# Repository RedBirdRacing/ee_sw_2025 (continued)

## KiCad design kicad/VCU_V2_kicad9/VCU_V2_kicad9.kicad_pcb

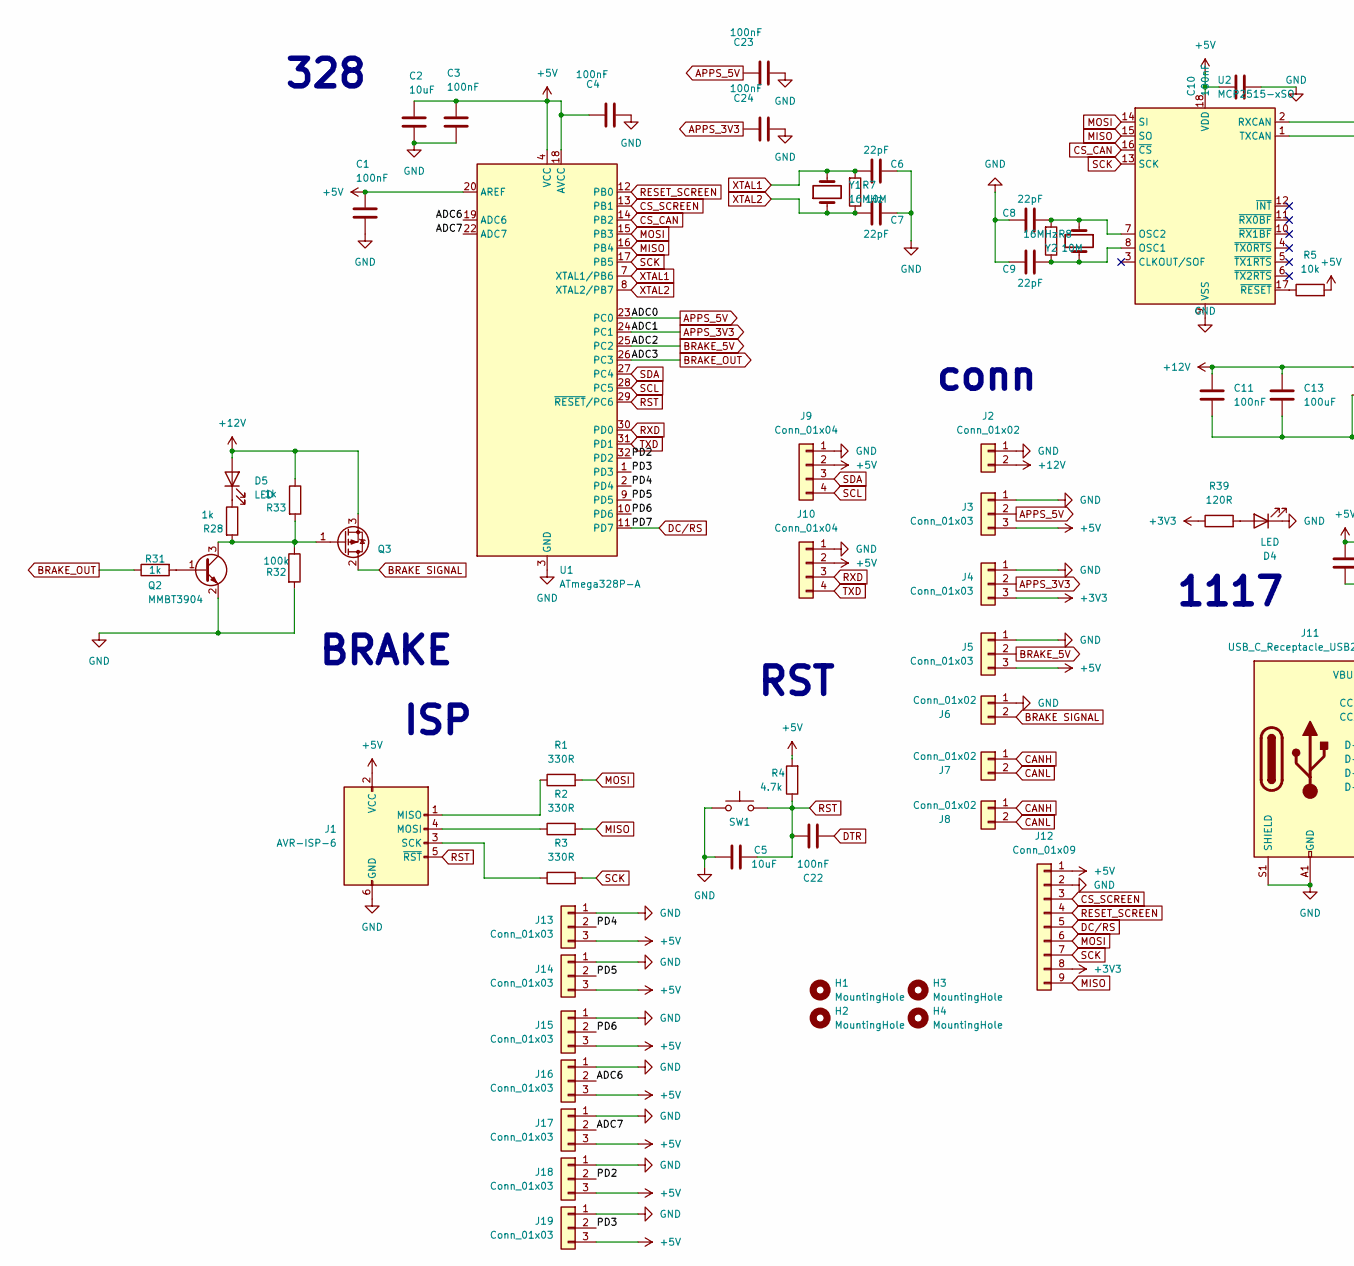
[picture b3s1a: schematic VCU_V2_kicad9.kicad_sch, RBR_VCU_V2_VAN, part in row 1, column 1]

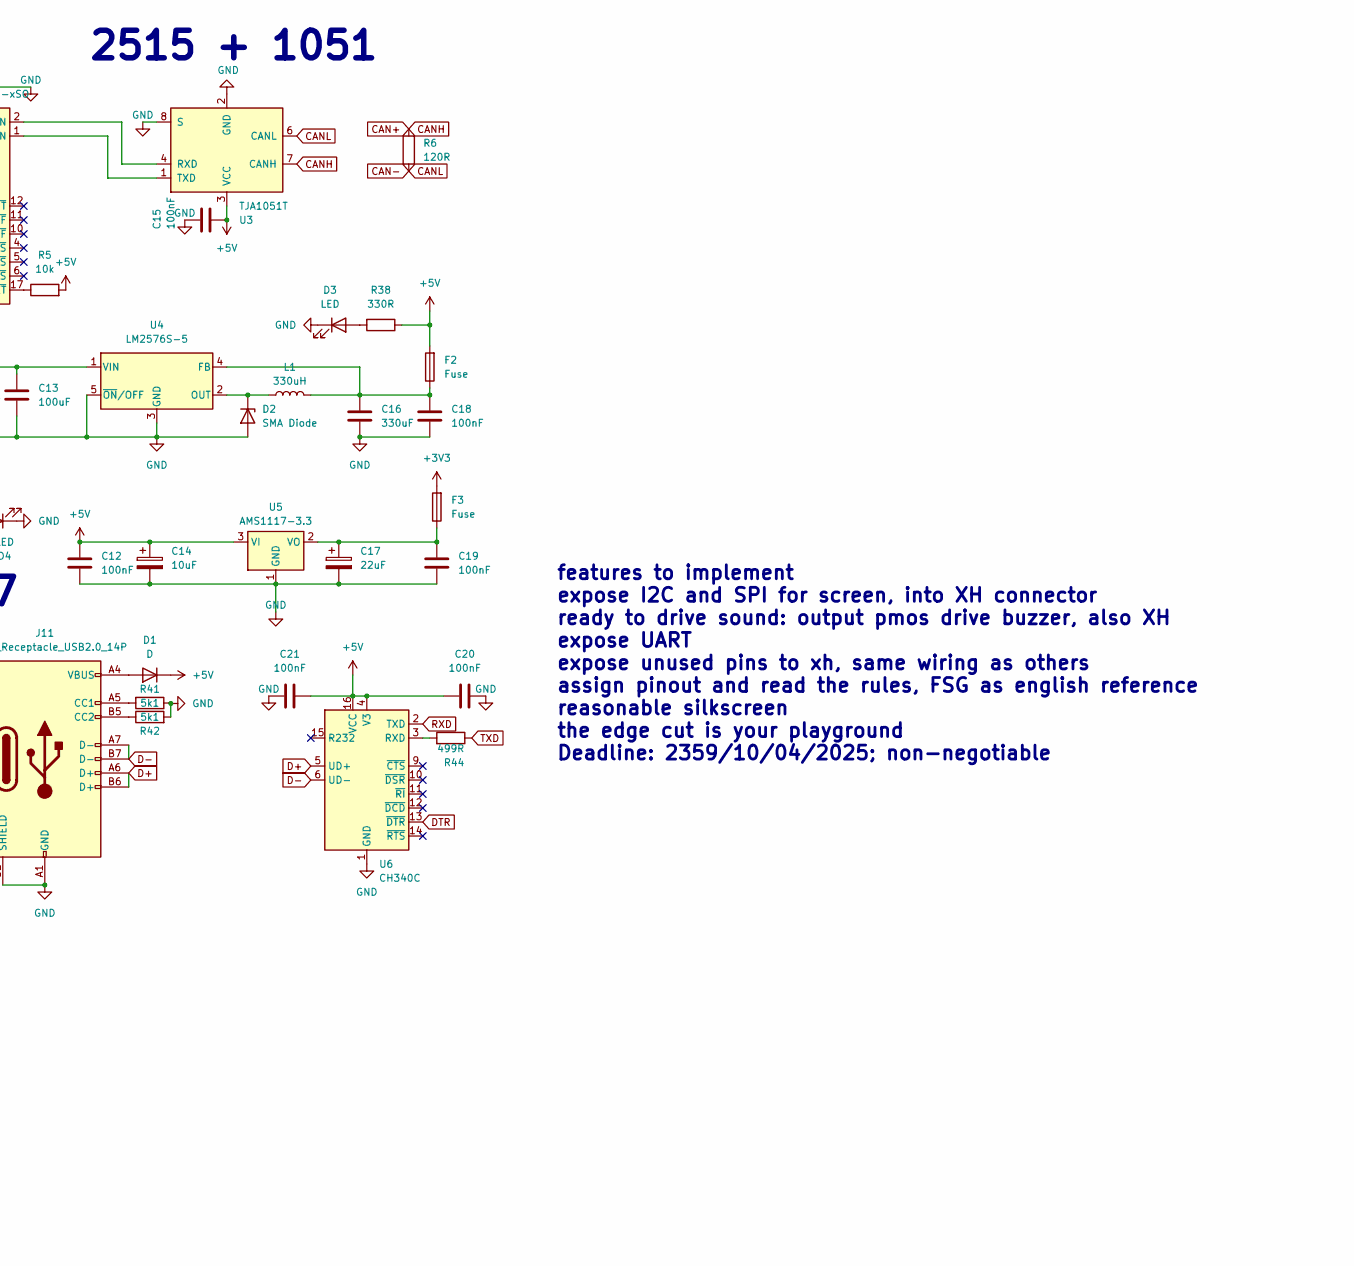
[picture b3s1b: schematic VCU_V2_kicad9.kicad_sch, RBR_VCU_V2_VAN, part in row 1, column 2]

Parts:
C1, C3, C4, C10, C11, C12, C15, C18, C19, C20, C21, C22, C23, C24: 100nF; C_0805_2012Metric_Pad1.18x1.45mm_HandSolder_L
C2, C5, C14: 10uF; C_0805_2012Metric_Pad1.18x1.45mm_HandSolder_L
C6, C7, C8, C9: 22pF; C_0805_2012Metric_Pad1.18x1.45mm_HandSolder_L
C13: 100uF; CP_Radial_D6.3mm_P2.50mm
C16: 330uF; CP_Radial_D6.3mm_P2.50mm
C17: 22uF; C_0805_2012Metric_Pad1.18x1.45mm_HandSolder_L
D1: D; D_SMA_Handsoldering
D2: SMA Diode; D_SMA_Handsoldering
D3, D4, D5: LED; LED_0805_2012Metric_Pad1.45x1.40mm_HandSolder
F2, F3: Fuse; Fuse_1210_3225Metric_Pad1.42x2.65mm_HandSolder
H1, H2, H3, H4: MountingHole; MountingHole_3.2mm_M3
J1: AVR-ISP-6; PinHeader_2x03_P2.54mm_Vertical
J2: Conn_01x02; JST_VH_B2P-VH-B_1x02_P3.96mm_Vertical
J3, J4, J5, J13, J14, J15, J16, J17, J18, J19: Conn_01x03; JST_XH_B3B-XH-A_1x03_P2.50mm_Vertical
J6, J7, J8: Conn_01x02; JST_XH_B2B-XH-A_1x02_P2.50mm_Vertical
J9, J10: Conn_01x04; JST_XH_B4B-XH-A_1x04_P2.50mm_Vertical
J11: USB_C_Receptacle_USB2.0_14P; USB_C_Receptacle_G-Switch_GT-USB-7010ASV_Handsolder
J12: Conn_01x09; JST_XH_B9B-XH-A_1x09_P2.50mm_Vertical
L1: 330uH; L_10.4x10.4_H4.8
Q2: MMBT3904; SOT-23
Q3: TO-252 PMOS; TO-252-2
R1, R2, R3, R38: 330R; R_0805_2012Metric_Pad1.20x1.40mm_HandSolder_L
R4: 4.7k; R_0805_2012Metric_Pad1.20x1.40mm_HandSolder_L
R5: 10k; R_0805_2012Metric_Pad1.20x1.40mm_HandSolder_L
R6, R39: 120R; R_0805_2012Metric_Pad1.20x1.40mm_HandSolder_L
R7, R8: 10M; R_0805_2012Metric_Pad1.20x1.40mm_HandSolder_L
R28, R31, R33: 1k; R_0805_2012Metric_Pad1.20x1.40mm_HandSolder_L
R32: 100k; R_0805_2012Metric_Pad1.20x1.40mm_HandSolder_L
R41, R42: 5k1; R_0805_2012Metric_Pad1.20x1.40mm_HandSolder_L
R44: 499R; R_0805_2012Metric_Pad1.20x1.40mm_HandSolder_L
SW1: SW_Push; SW_PUSH_6mm_H5mm
U1: ATmega328P-A; TQFP-32_7x7mm_P0.8mm_L
U2: MCP2515-xSO; SOIC-18W_7.5x11.6mm_P1.27mm_L
U3: TJA1051T; SOIC-8_3.9x4.9mm_P1.27mm_RMC_Handsolder
U4: LM2576S-5; TO-263-5_TabPin3_Handsolder
U5: AMS1117-3.3; SOT-223-3_TabPin2_Handsolder
U6: CH340C; SOIC-16_3.9x9.9mm_P1.27mm_Handsolder
Y1, Y2: 16MHz; Crystal_HC49-U_Vertical_W_SMD

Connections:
+3V3: F3.2, J4.3, J12.8, R39.1
+5V: C1.2, C2.2, C3.2, C4.2, C10.2, C12.1, C14.1, C15.1, C20.1, C21.2, D1.1 (K), F2.2, J1.2 (VCC), J3.3, J5.3, J9.2, J10.2, J12.1, J13.3, J14.3, J15.3, J16.3, J17.3, J18.3, J19.3, R4.2, R5.2, R38.1, U1.4 (VCC), U1.6 (VCC), U1.18 (AVCC), U1.20 (AREF), U2.18 (VDD), U3.3 (VCC), U5.3 (VI), U6.4 (V3), U6.16 (VCC)
+12V: C11.2, C13.1, D5.2 (A), J2.2, Q3.3 (S), R33.1, U4.1 (VIN)
/ADC6: J16.2, U1.19 (ADC6)
/ADC7: J17.2, U1.22 (ADC7)
/PD2: J18.2, U1.32 (PD2)
/PD3: J19.2, U1.1 (PD3)
/PD4: J13.2, U1.2 (PD4)
/PD5: J14.2, U1.9 (PD5)
/PD6: J15.2, U1.10 (PD6)
APPS_3V3: C24.2, J4.2, U1.24 (PC1)
APPS_5V: C23.2, J3.2, U1.23 (PC0)
BRAKE SIGNAL: J6.2, Q3.2 (D)
BRAKE_5V: J5.2, U1.25 (PC2)
BRAKE_OUT: R31.1, U1.26 (PC3)
CAN+: J7.1, J8.1, R6.2, U3.7 (CANH)
CAN-: J7.2, J8.2, R6.1, U3.6 (CANL)
CS_CAN: U1.14 (PB2), U2.16 (~CS)
CS_SCREEN: J12.3, U1.13 (PB1)
D+: J11.A6 (D+), J11.B6 (D+), U6.5 (UD+)
D-: J11.A7 (D-), J11.B7 (D-), U6.6 (UD-)
DC/RS: J12.5, U1.11 (PD7)
DTR: C22.1, U6.13 (~DTR)
GND: C1.1, C2.1, C3.1, C4.1, C5.1, C6.1, C7.1, C8.1, C9.1, C10.1, C11.1, C12.2, C13.2, C14.2, C15.2, C16.2, C17.2, C18.1, C19.2, C20.2, C21.1, C23.1, C24.1, D2.2 (A), D3.1 (K), D4.1 (K), J1.6 (GND), J2.1, J3.1, J4.1, J5.1, J6.1, J9.1, J10.1, J11.A1 (GND), J11.A12 (GND), J11.B1 (GND), J11.B12 (GND), J11.S1 (SHIELD), J12.2, J13.1, J14.1, J15.1, J16.1, J17.1, J18.1, J19.1, Q2.2 (E), R32.2, R41.1, R42.2, SW1.1, U1.3 (GND), U1.5 (GND), U1.21 (GND), U2.9 (VSS), U3.2 (GND), U3.8 (S), U4.3 (GND), U4.5 (~ON/OFF), U5.1 (GND), U6.1 (GND)
MISO: J12.9, R2.2, U1.16 (PB4), U2.15 (SO)
MOSI: J12.6, R1.2, U1.15 (PB3), U2.14 (SI)
unnamed: D1.2 (A), J11.A4 (VBUS), J11.A9 (VBUS), J11.B4 (VBUS), J11.B9 (VBUS)
unnamed: D2.1 (K), L1.1, U4.2 (OUT)
unnamed: D3.2 (A), R38.2
unnamed: D4.2 (A), R39.2
unnamed: D5.1 (K), R28.1
unnamed: J1.1 (MISO), R1.1
unnamed: J1.4 (MOSI), R2.1
unnamed: J1.3 (SCK), R3.1
unnamed: J11.A5 (CC1), R41.2
unnamed: J11.B5 (CC2), R42.1
unnamed: Q2.1 (B), R31.2
unnamed: Q2.3 (C), Q3.1 (G), R28.2, R32.1, R33.2
unnamed: C9.2, R8.1, U2.8 (OSC1), Y2.2
unnamed: C8.2, R8.2, U2.7 (OSC2), Y2.1
unnamed: U2.2 (RXCAN), U3.4 (RXD)
unnamed: U2.1 (TXCAN), U3.1 (TXD)
unnamed: R5.1, U2.17 (~RESET)
unnamed: C16.1, C18.2, F2.1, L1.2, U4.4 (FB)
unnamed: C17.1, C19.1, F3.1, U5.2 (VO)
unnamed: R44.2, U6.3 (RXD)
RESET_SCREEN: J12.4, U1.12 (PB0)
RST: C5.2, C22.2, J1.5 (~RST), R4.1, SW1.2, U1.29 (~RESET/PC6)
RXD: J10.3, U1.30 (PD0), U6.2 (TXD)
SCK: J12.7, R3.2, U1.17 (PB5), U2.13 (SCK)
SCL: J9.4, U1.28 (PC5)
SDA: J9.3, U1.27 (PC4)
TXD: J10.4, R44.1, U1.31 (PD1)
XTAL1: C6.2, R7.2, U1.7 (XTAL1/PB6), Y1.2
XTAL2: C7.2, R7.1, U1.8 (XTAL2/PB7), Y1.1

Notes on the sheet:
RST
conn
ISP
1117
2515 + 1051
features to implement expose I2C and SPI for screen, into XH connector ready to drive sound: output pmos drive buzzer, also XH expose UART expose unused pins to xh, same wiring as others assign pinout and read the rules, FSG as english reference reasonable silkscreen the edge cut is your playground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
BRAKE
328

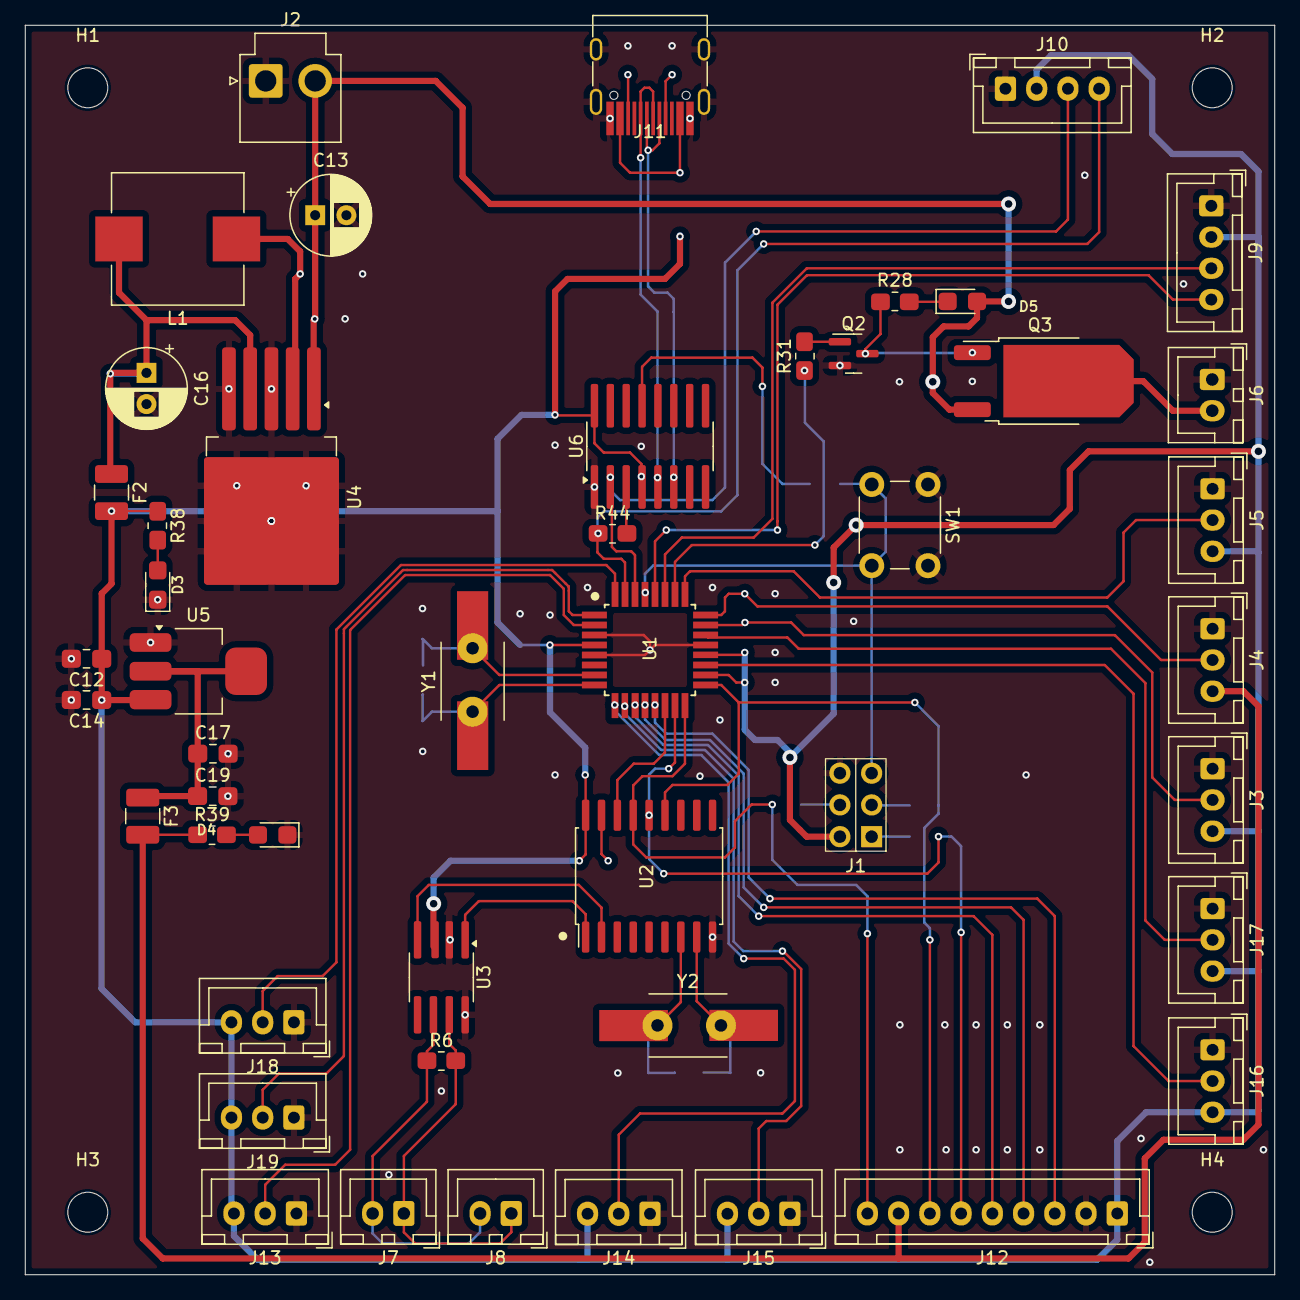
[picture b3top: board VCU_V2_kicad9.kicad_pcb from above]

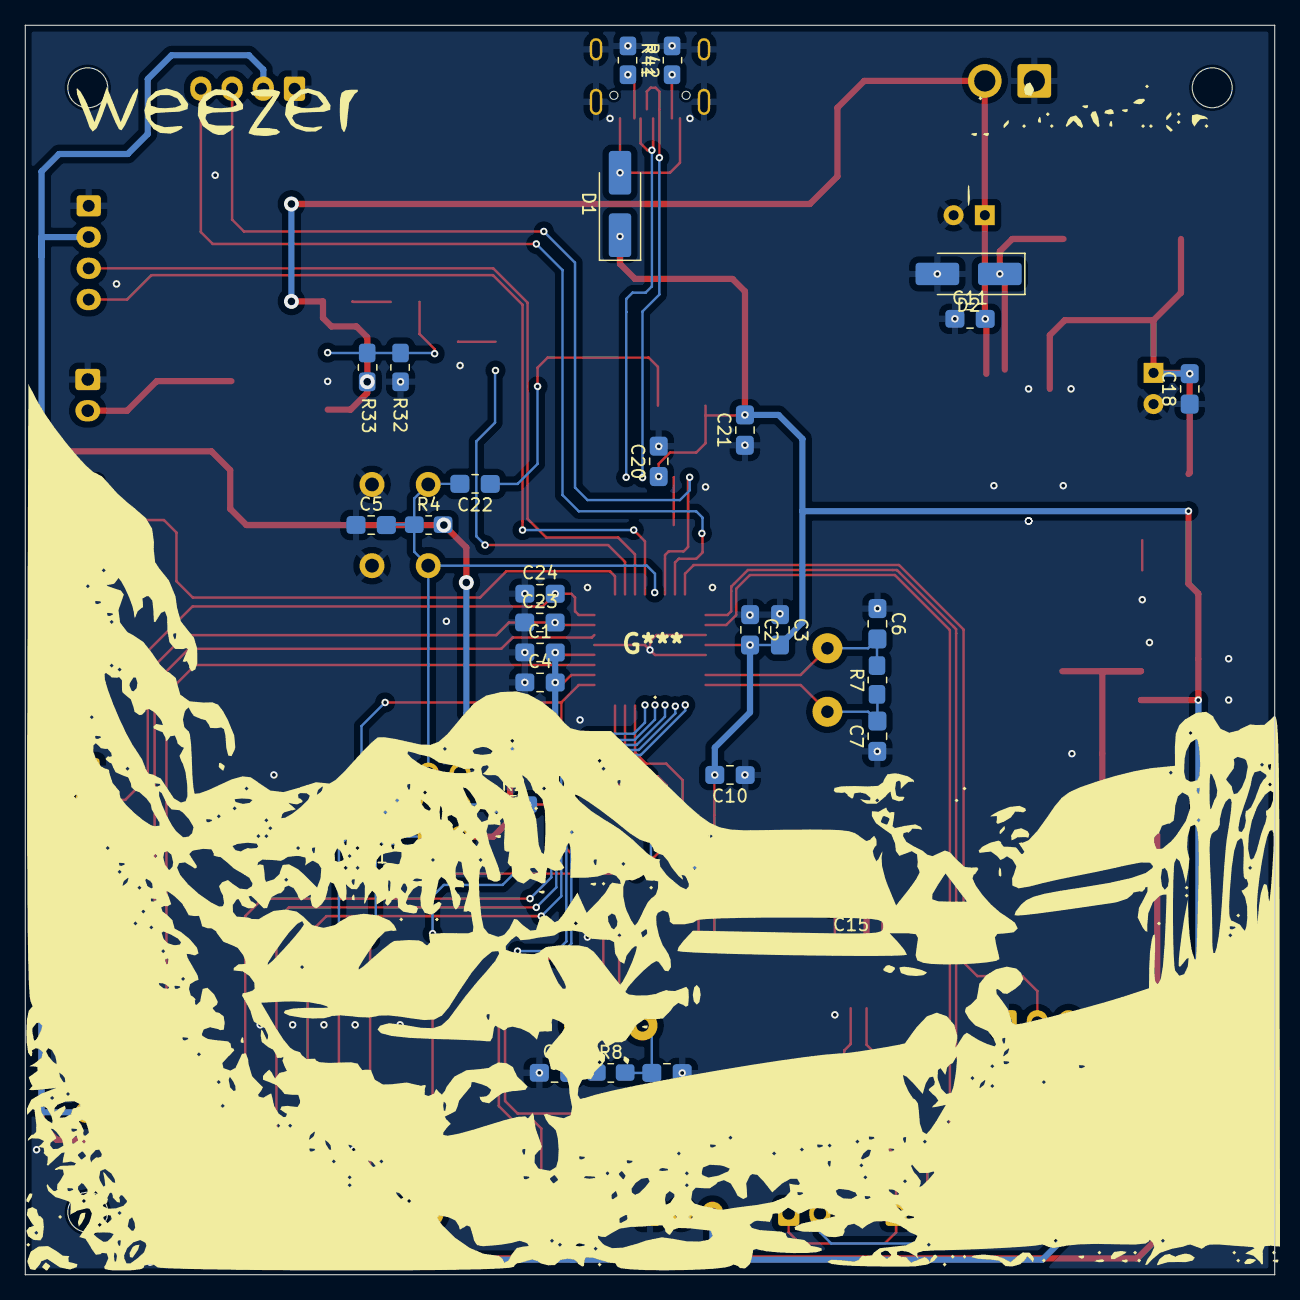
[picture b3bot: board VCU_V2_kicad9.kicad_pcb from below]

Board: 2 copper layers, 100.0 x 100.0 mm, 83 parts (31 on the bottom side), 55 nets.

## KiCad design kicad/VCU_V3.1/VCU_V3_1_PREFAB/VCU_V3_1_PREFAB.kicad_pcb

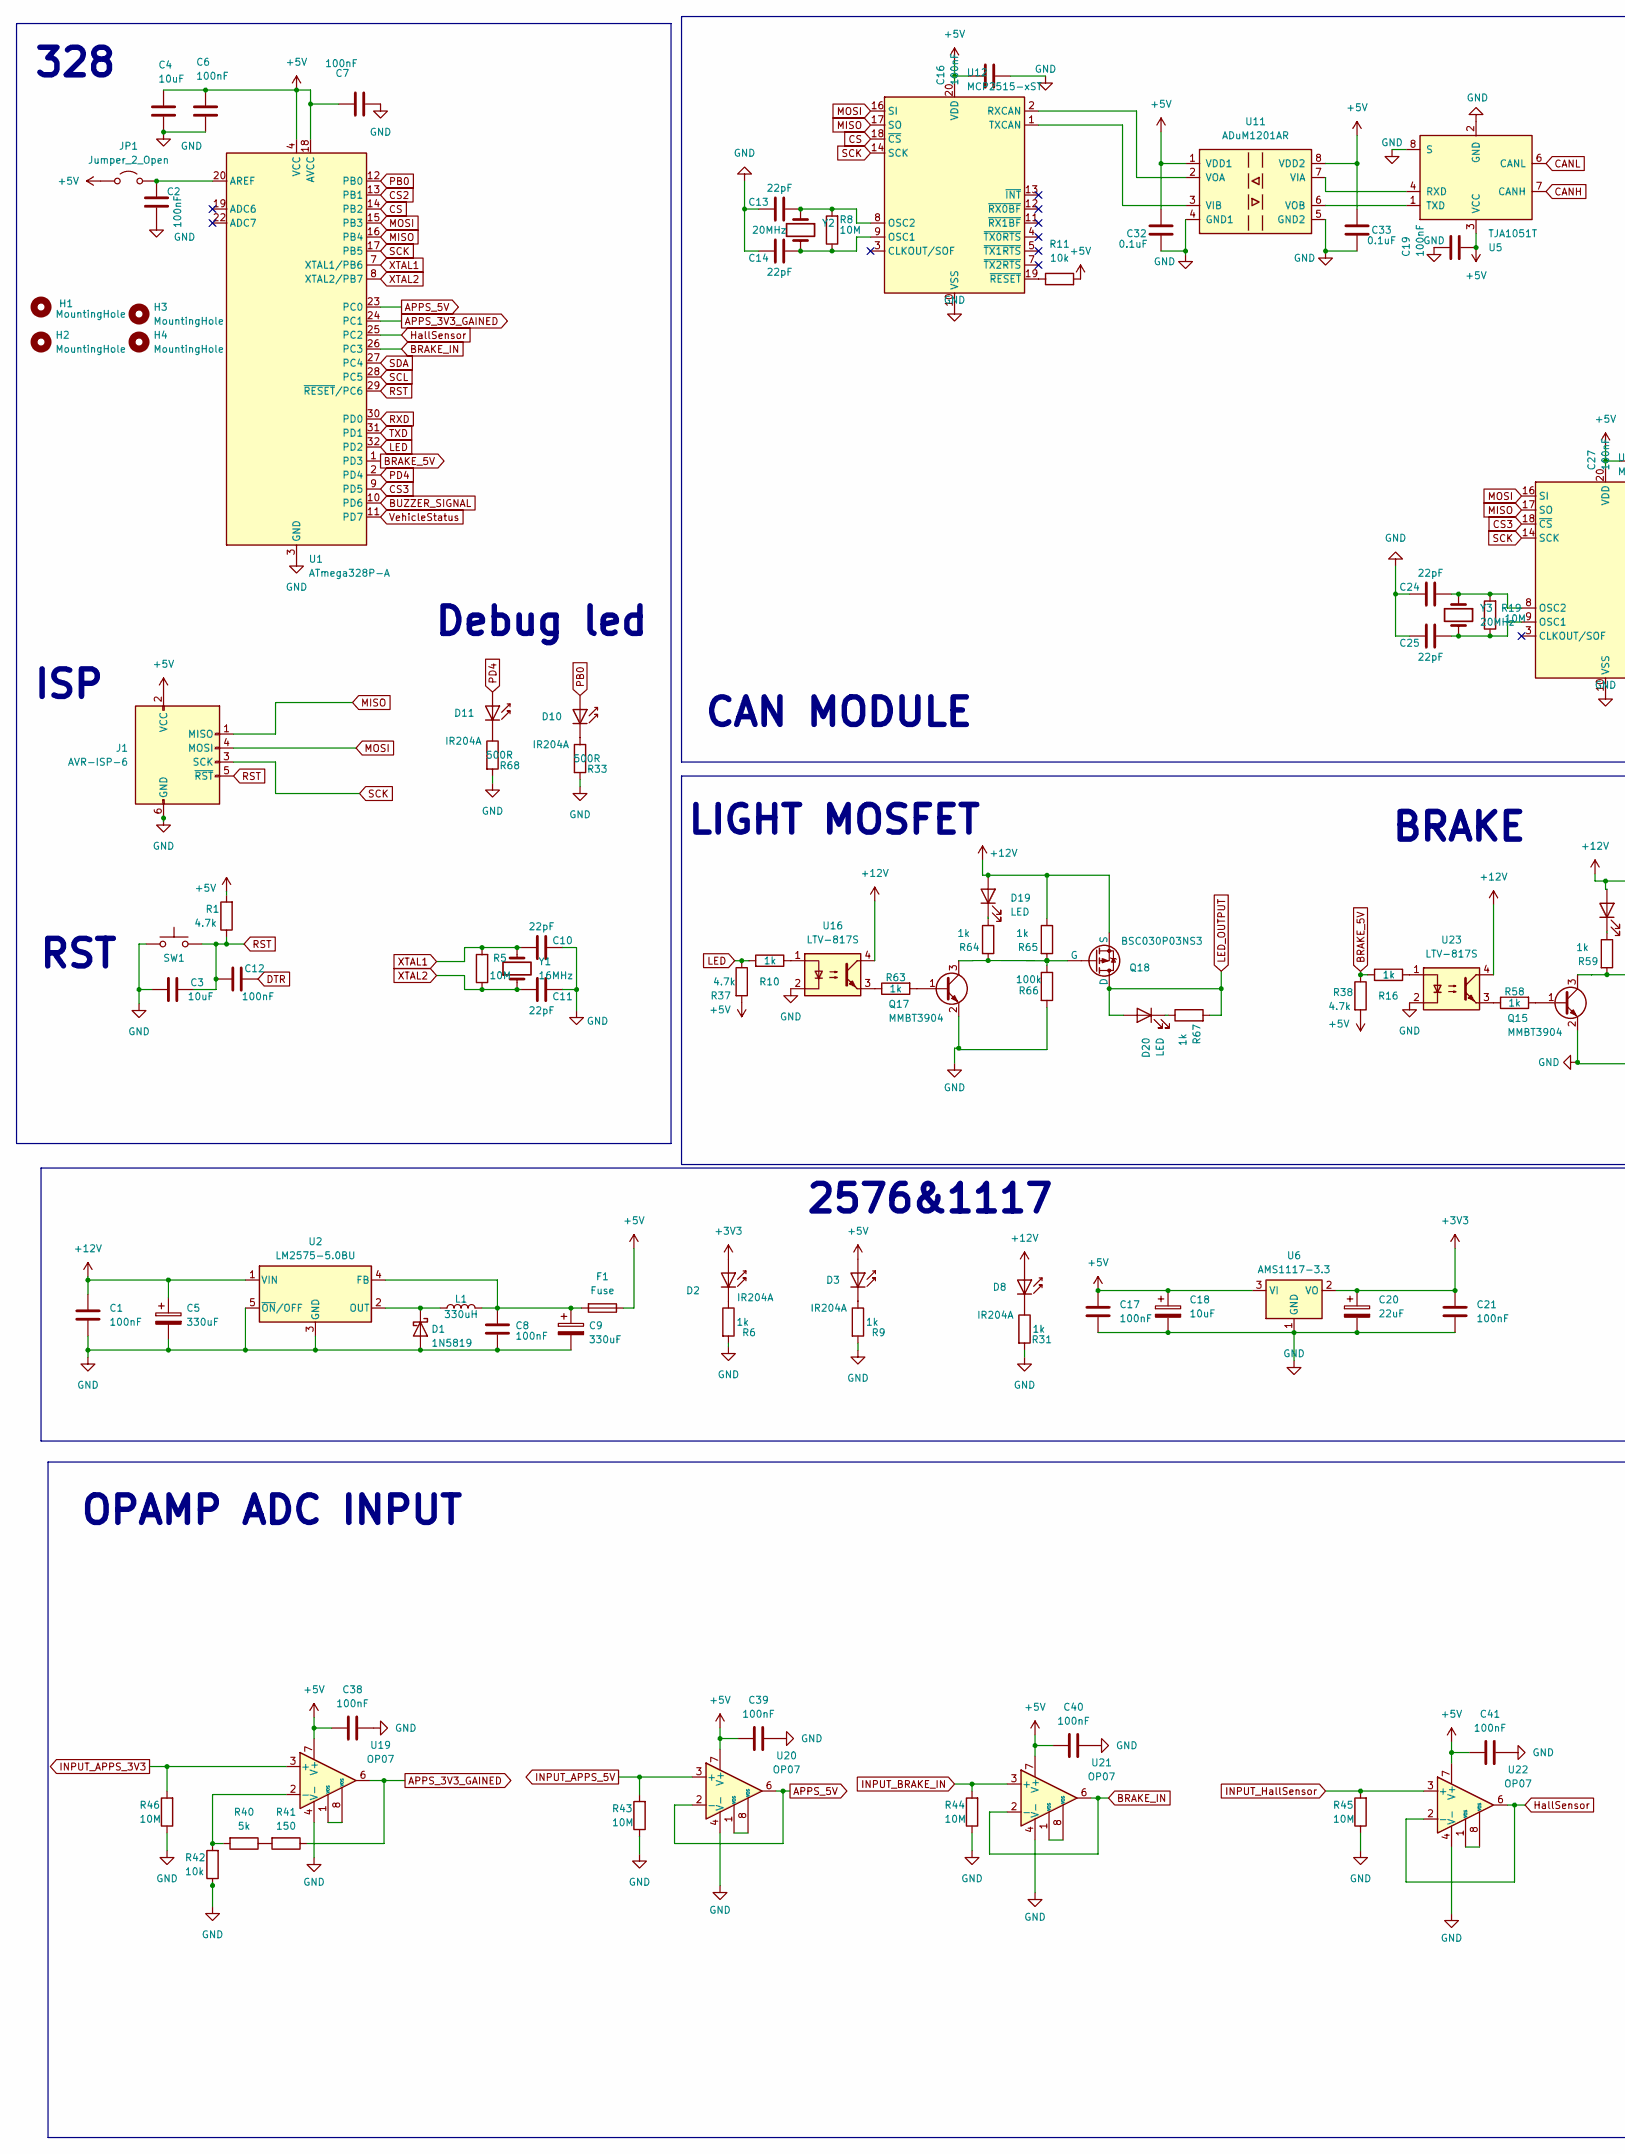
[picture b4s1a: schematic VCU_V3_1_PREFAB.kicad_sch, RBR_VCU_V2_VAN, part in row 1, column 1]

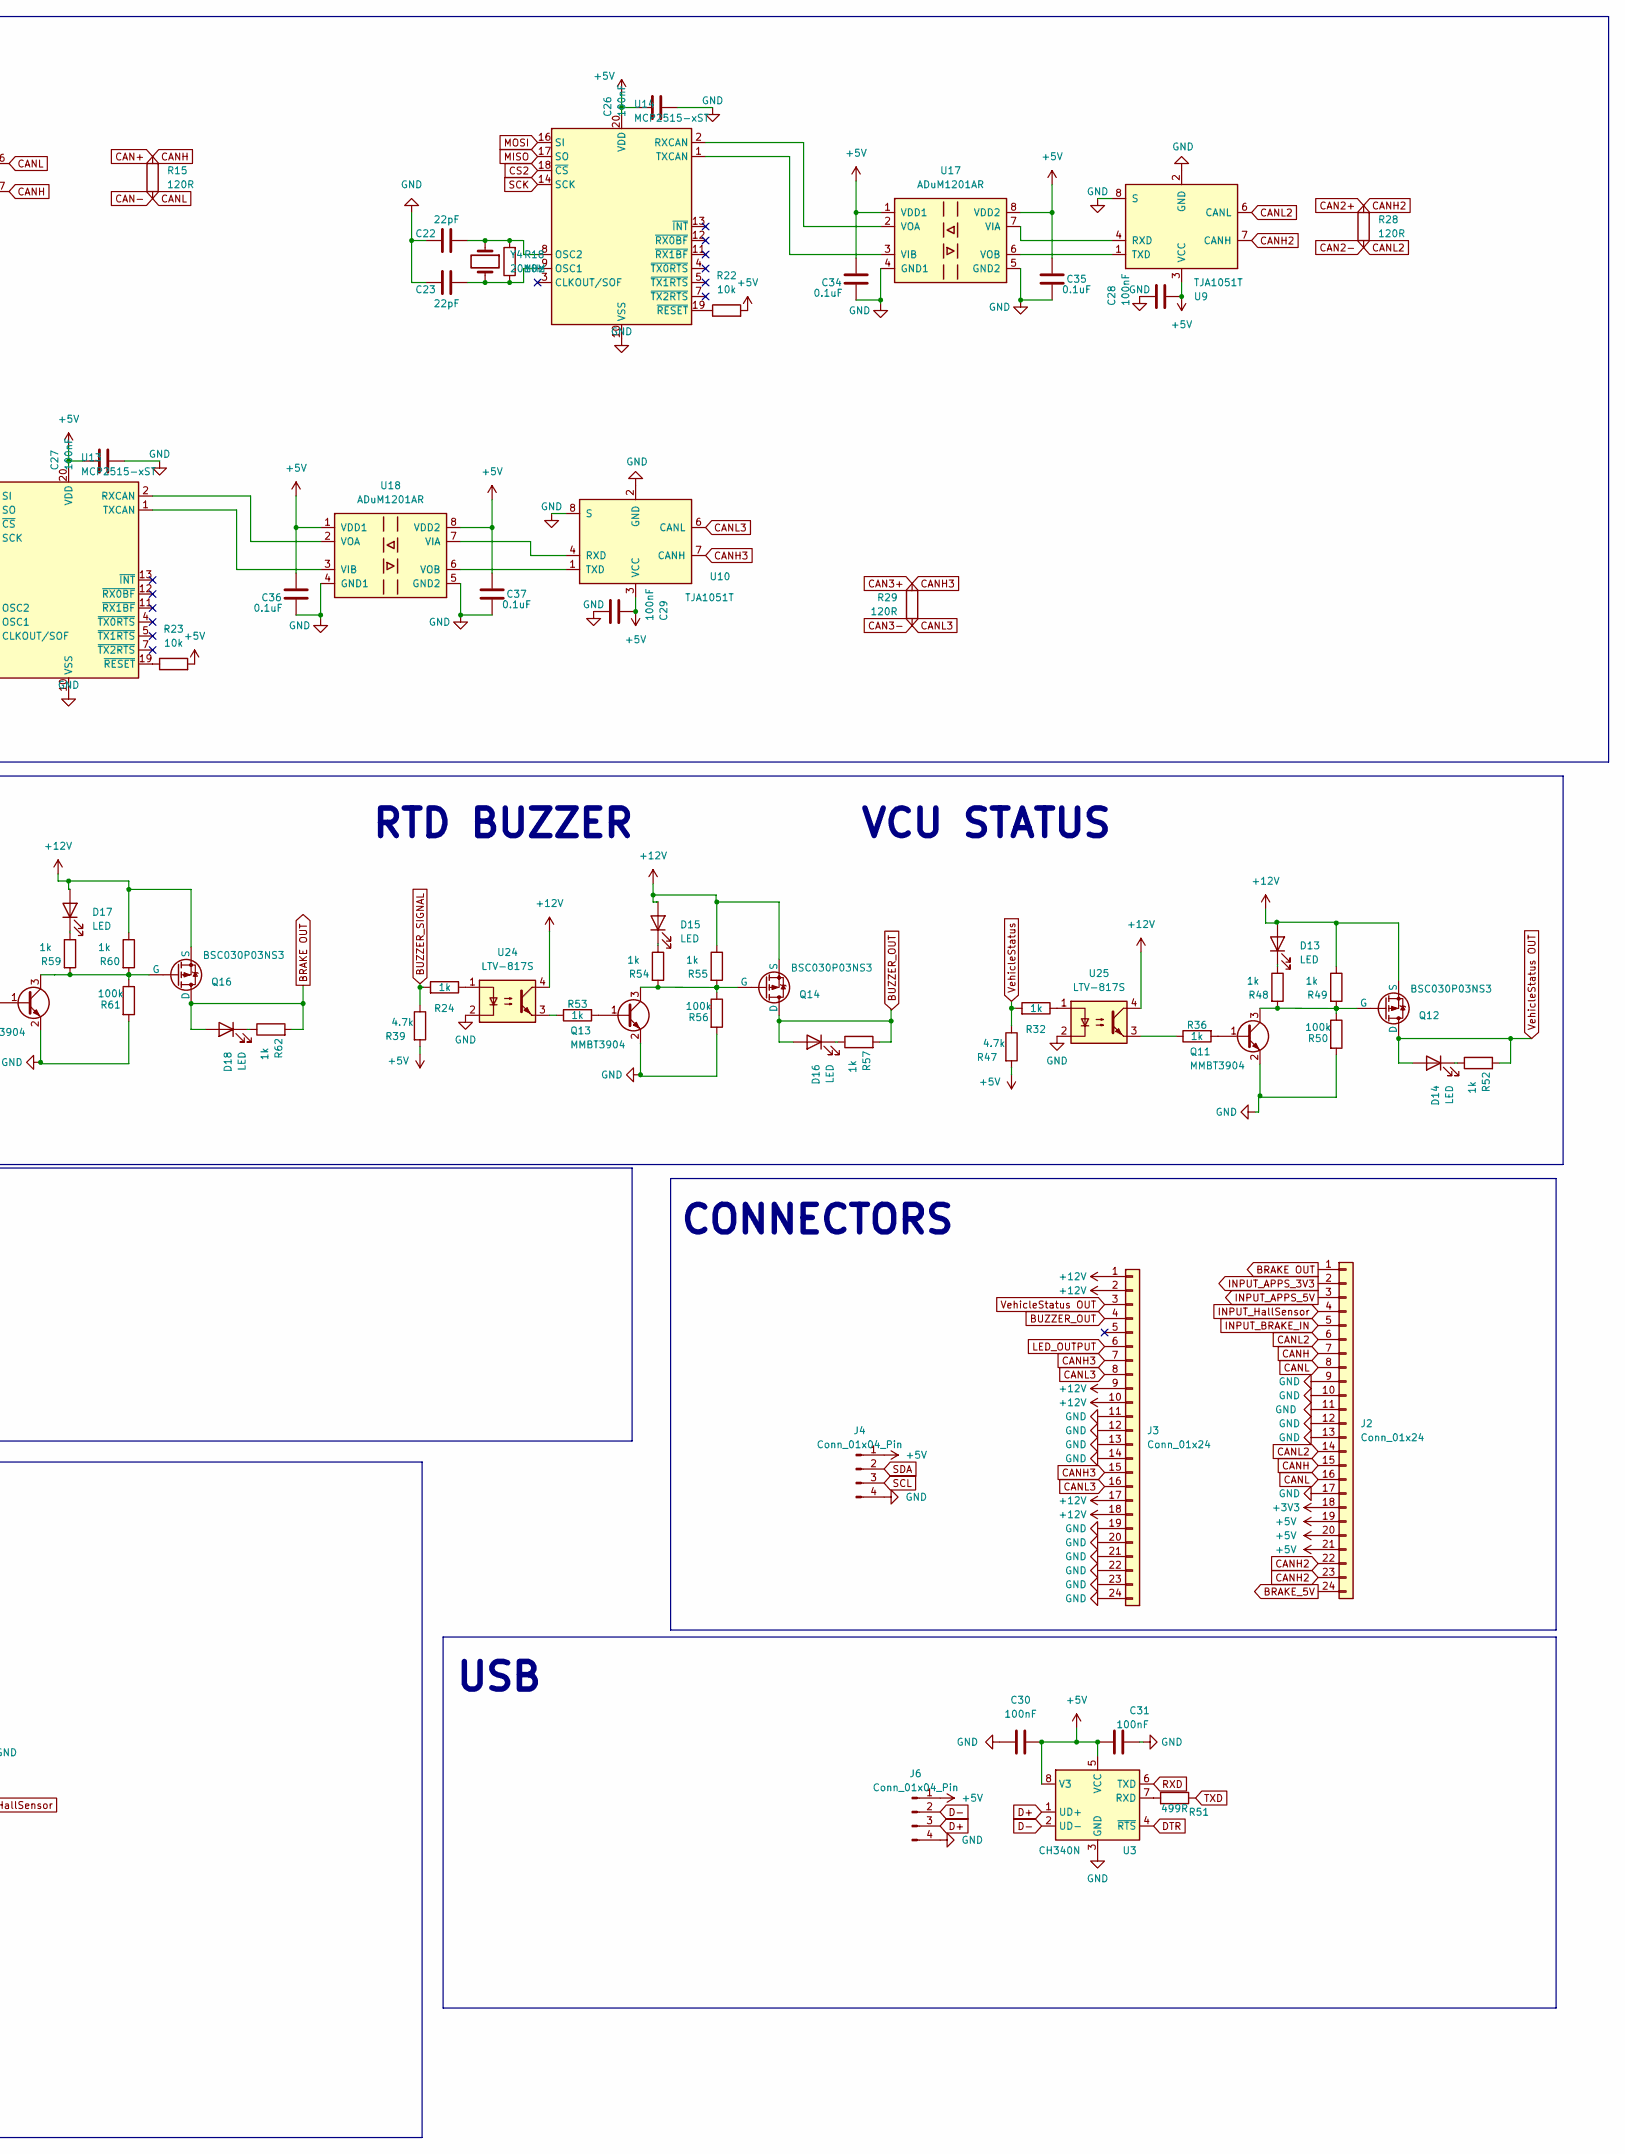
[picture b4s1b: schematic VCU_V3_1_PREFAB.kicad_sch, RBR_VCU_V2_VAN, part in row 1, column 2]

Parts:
C1, C2, C6, C7, C8, C12, C16, C17, C19, C21, C26, C27, C28, C29, C30, C31, C38, C39, C40, C41: 100nF; C_0805_2012Metric_Pad1.18x1.45mm_HandSolder_L
C3, C4, C18: 10uF; C_0805_2012Metric_Pad1.18x1.45mm_HandSolder_L
C5, C9: 330uF; CP_Radial_D10.0mm_P5.00mm_F
C10, C11, C13, C14, C22, C23, C24, C25: 22pF; C_0805_2012Metric_Pad1.18x1.45mm_HandSolder_L
C20: 22uF; C_0805_2012Metric_Pad1.18x1.45mm_HandSolder_L
C32, C33, C34, C35, C36, C37: 0.1uF; C_0805_2012Metric_Pad1.18x1.45mm_HandSolder_L
D1: 1N5819; D_SMA_Handsoldering
D2, D3, D8, D10, D11: IR204A; LED_1206_3216Metric_Pad1.42x1.75mm_HandSolder
D13, D14, D15, D16, D17, D18, D19, D20: LED; LED_0805_2012Metric_Pad1.45x1.40mm_HandSolder
F1: Fuse; Fuse_1210_3225Metric_Pad1.42x2.65mm_HandSolder
H1, H2, H3, H4: MountingHole; MountingHole_3.2mm_M3
J1: AVR-ISP-6; PinHeader_2x03_P2.54mm_Vertical
J2, J3: Conn_01x24; HD241_24pin
J4, J6: Conn_01x04_Pin; JST_XH_B4B-XH-A_1x04_P2.50mm_Vertical
JP1: Jumper_2_Open; SolderJumper-2_P1.3mm_Open_Pad1.0x1.5mm
L1: 330uH; L_TDK_SLF12575
Q11, Q13, Q15, Q17: MMBT3904; SOT-23
Q12, Q14, Q16, Q18: BSC030P03NS3; Infineon_PG-TDSON-8_6.15x5.15mm
R1, R37, R38, R39, R47: 4.7k; R_0805_2012Metric_Pad1.20x1.40mm_HandSolder_L
R5, R8, R18, R19, R43, R44, R45, R46: 10M; R_0805_2012Metric_Pad1.20x1.40mm_HandSolder_L
R6, R9, R10, R16, R24, R31, R32, R36, R48, R49, R52, R53, R54, R55, R57, R58, R59, R60, R62, R63, R64, R65, R67: 1k; R_0805_2012Metric_Pad1.20x1.40mm_HandSolder_L
R11, R22, R23, R42: 10k; R_0805_2012Metric_Pad1.20x1.40mm_HandSolder_L
R15, R28, R29: 120R; R_0805_2012Metric_Pad1.20x1.40mm_HandSolder_L
R33, R68: 500R; R_0805_2012Metric_Pad1.20x1.40mm_HandSolder_L
R40: 5k; R_0805_2012Metric_Pad1.20x1.40mm_HandSolder_L
R41: 150; R_0805_2012Metric_Pad1.20x1.40mm_HandSolder_L
R50, R56, R61, R66: 100k; R_0805_2012Metric_Pad1.20x1.40mm_HandSolder_L
R51: 499R; R_0805_2012Metric_Pad1.20x1.40mm_HandSolder_L
SW1: SW_Push; SW_PUSH_6mm_H5mm
U1: ATmega328P-A; TQFP-32_7x7mm_P0.8mm_L
U2: LM2575-5.0BU; TO-263-5_TabPin3
U3: CH340N; SOIC-8_3.9x4.9mm_P1.27mm_RMC_Handsolder
U5, U9, U10: TJA1051T; SOIC-8_3.9x4.9mm_P1.27mm_RMC_Handsolder
U6: AMS1117-3.3; SOT-223-3_TabPin2_Handsolder
U11, U17, U18: ADuM1201AR; SOIC-8_3.9x4.9mm_P1.27mm_RMC_Handsolder
U12, U13, U14: MCP2515-xST; TSSOP-20_4.4x6.5mm_P0.65mm
U16, U23, U24, U25: LTV-817S; SMDIP-4_W9.53mm
U19, U20, U21, U22: OP07; SOIC-8_3.9x4.9mm_P1.27mm_RMC_Handsolder
Y1: 16MHz; Crystal_HC49-U_Vertical_W_SMD
Y2, Y3, Y4: 20MHz; Crystal_HC49-U_Vertical_W_SMD

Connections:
+3V3: C20.1, C21.1, D2.2 (A), J2.18, U6.2 (VO)
+5V: C4.2, C6.2, C7.2, C16.2, C17.1, C18.1, C19.1, C26.2, C27.2, C28.1, C29.2, C30.2, C31.1, C32.2, C33.2, C34.2, C35.2, C36.2, C37.2, C38.1, C39.1, C40.1, C41.1, D3.2 (A), F1.1, J1.2 (VCC), J2.19, J2.20, J2.21, J4.1, J6.1, JP1.1 (A), R1.2, R11.2, R22.2, R23.2, R37.2, R38.2, R39.2, R47.2, U1.4 (VCC), U1.6 (VCC), U1.18 (AVCC), U3.5 (VCC), U3.8 (V3), U5.3 (VCC), U6.3 (VI), U9.3 (VCC), U10.3 (VCC), U11.1 (VDD1), U11.8 (VDD2), U12.20 (VDD), U13.20 (VDD), U14.20 (VDD), U17.1 (VDD1), U17.8 (VDD2), U18.1 (VDD1), U18.8 (VDD2), U19.7 (V+), U20.7 (V+), U21.7 (V+), U22.7 (V+)
+12V: C1.1, C5.1, D8.2 (A), D13.2 (A), D15.2 (A), D17.2 (A), D19.2 (A), J3.1, J3.2, J3.9, J3.10, J3.17, J3.18, Q12.1 (S), Q12.2 (S), Q12.3 (S), Q14.1 (S), Q14.2 (S), Q14.3 (S), Q16.1 (S), Q16.2 (S), Q16.3 (S), Q18.1 (S), Q18.2 (S), Q18.3 (S), R49.1, R55.1, R60.1, R65.1, U2.1 (VIN), U16.4, U23.4, U24.4, U25.4
APPS_3V3_GAINED: R41.1, U1.24 (PC1), U19.6
APPS_5V: U1.23 (PC0), U20.2 (-), U20.6
BRAKE OUT: D18.2 (A), J2.1, Q16.5 (D), Q16.6 (D), Q16.7 (D), Q16.8 (D), R62.2
BRAKE_5V: J2.24, R16.2, R38.1, U1.1 (PD3)
BRAKE_IN: U1.26 (PC3), U21.2 (-), U21.6
BUZZER_OUT: D16.2 (A), J3.4, Q14.5 (D), Q14.6 (D), Q14.7 (D), Q14.8 (D), R57.2
BUZZER_SIGNAL: R24.2, R39.1, U1.10 (PD6)
CAN2+: J2.22, J2.23, R28.2, U9.7 (CANH)
CAN2-: J2.6, J2.14, R28.1, U9.6 (CANL)
CAN3+: J3.7, J3.15, R29.2, U10.7 (CANH)
CAN3-: J3.8, J3.16, R29.1, U10.6 (CANL)
CAN+: J2.7, J2.15, R15.2, U5.7 (CANH)
CAN-: J2.8, J2.16, R15.1, U5.6 (CANL)
CS: U1.14 (PB2), U12.18 (~CS)
CS2: U1.13 (PB1), U14.18 (~CS)
CS3: U1.9 (PD5), U13.18 (~CS)
D+: J6.3, U3.1 (UD+)
D-: J6.2, U3.2 (UD-)
DTR: C12.2, U3.4 (~RTS)
GND: C1.2, C2.2, C3.1, C4.1, C5.2, C6.1, C7.1, C8.2, C9.2, C10.1, C11.1, C13.1, C14.1, C16.1, C17.2, C18.2, C19.2, C20.2, C21.2, C22.1, C23.1, C24.1, C25.1, C26.1, C27.1, C28.2, C29.1, C30.1, C31.2, C32.1, C33.1, C34.1, C35.1, C36.1, C37.1, C38.2, C39.2, C40.2, C41.2, D1.2 (A), J1.6 (GND), J2.9, J2.10, J2.11, J2.12, J2.13, J2.17, J3.11, J3.12, J3.13, J3.14, J3.19, J3.20, J3.21, J3.22, J3.23, J3.24, J4.4, J6.4, Q11.2 (E), Q13.2 (E), Q15.2 (E), Q17.2 (E), R6.2, R9.2, R31.2, R33.2, R42.1, R43.1, R44.1, R45.1, R46.1, R50.2, R56.2, R61.2, R66.2, R68.2, SW1.1, U1.3 (GND), U1.5 (GND), U1.21 (GND), U2.3 (GND), U2.5 (~ON/OFF), U3.3 (GND), U5.2 (GND), U5.8 (S), U6.1 (GND), U9.2 (GND), U9.8 (S), U10.2 (GND), U10.8 (S), U11.4 (GND1), U11.5 (GND2), U12.10 (VSS), U13.10 (VSS), U14.10 (VSS), U16.2, U17.4 (GND1), U17.5 (GND2), U18.4 (GND1), U18.5 (GND2), U19.4 (V-), U20.4 (V-), U21.4 (V-), U22.4 (V-), U23.2, U24.2, U25.2
HallSensor: U1.25 (PC2), U22.2 (-), U22.6
INPUT_APPS_3V3: J2.2, R46.2, U19.3 (+)
INPUT_APPS_5V: J2.3, R43.2, U20.3 (+)
INPUT_BRAKE_IN: J2.5, R44.2, U21.3 (+)
INPUT_HallSensor: J2.4, R45.2, U22.3 (+)
LED: R10.2, R37.1, U1.32 (PD2)
LED_OUTPUT: D20.2 (A), J3.6, Q18.5 (D), Q18.6 (D), Q18.7 (D), Q18.8 (D), R67.2
MISO: J1.1 (MISO), U1.16 (PB4), U12.17 (SO), U13.17 (SO), U14.17 (SO)
MOSI: J1.4 (MOSI), U1.15 (PB3), U12.16 (SI), U13.16 (SI), U14.16 (SI)
unnamed: D1.1 (K), L1.1, U2.2 (OUT)
unnamed: D2.1 (K), R6.1
unnamed: D3.1 (K), R9.1
unnamed: D8.1 (K), R31.1
unnamed: D10.1 (K), R33.1
unnamed: D11.1 (K), R68.1
unnamed: D13.1 (K), R48.1
unnamed: D14.1 (K), R52.1
unnamed: D15.1 (K), R54.1
unnamed: D16.1 (K), R57.1
unnamed: D17.1 (K), R59.1
unnamed: D18.1 (K), R62.1
unnamed: D19.1 (K), R64.1
unnamed: D20.1 (K), R67.1
unnamed: C2.1, JP1.2 (B), U1.20 (AREF)
unnamed: Q11.1 (B), R36.2
unnamed: Q11.3 (C), Q12.4 (G), R48.2, R49.2, R50.1
unnamed: Q13.1 (B), R53.2
unnamed: Q13.3 (C), Q14.4 (G), R54.2, R55.2, R56.1
unnamed: Q15.1 (B), R58.2
unnamed: Q15.3 (C), Q16.4 (G), R59.2, R60.2, R61.1
unnamed: Q17.1 (B), R63.2
unnamed: Q17.3 (C), Q18.4 (G), R64.2, R65.2, R66.1
unnamed: R10.1, U16.1
unnamed: R16.1, U23.1
unnamed: R24.1, U24.1
unnamed: R32.1, U25.1
unnamed: R36.1, U25.3
unnamed: R40.1, R41.2
unnamed: R53.1, U24.3
unnamed: R58.1, U23.3
unnamed: R63.1, U16.3
unnamed: C8.1, C9.1, F1.2, L1.2, U2.4 (FB)
unnamed: R51.2, U3.7 (RXD)
unnamed: U10.4 (RXD), U18.7 (VIA)
unnamed: U10.1 (TXD), U18.6 (VOB)
unnamed: U5.4 (RXD), U11.7 (VIA)
unnamed: U11.3 (VIB), U12.1 (TXCAN)
unnamed: U11.2 (VOA), U12.2 (RXCAN)
unnamed: U5.1 (TXD), U11.6 (VOB)
unnamed: C14.2, R8.1, U12.9 (OSC1), Y2.2
unnamed: C13.2, R8.2, U12.8 (OSC2), Y2.1
unnamed: R11.1, U12.19 (~RESET)
unnamed: C25.2, R19.1, U13.9 (OSC1), Y3.2
unnamed: C24.2, R19.2, U13.8 (OSC2), Y3.1
unnamed: U13.2 (RXCAN), U18.2 (VOA)
unnamed: U13.1 (TXCAN), U18.3 (VIB)
unnamed: R23.1, U13.19 (~RESET)
unnamed: C23.2, R18.1, U14.9 (OSC1), Y4.2
unnamed: C22.2, R18.2, U14.8 (OSC2), Y4.1
unnamed: U14.2 (RXCAN), U17.2 (VOA)
unnamed: U14.1 (TXCAN), U17.3 (VIB)
unnamed: R22.1, U14.19 (~RESET)
unnamed: U9.4 (RXD), U17.7 (VIA)
unnamed: U9.1 (TXD), U17.6 (VOB)
unnamed: R40.2, R42.2, U19.2 (-)
unnamed: U19.1 (VOS), U19.8 (VOS)
unnamed: U20.1 (VOS), U20.8 (VOS)
unnamed: U21.1 (VOS), U21.8 (VOS)
unnamed: U22.1 (VOS), U22.8 (VOS)
PB0: D10.2 (A), U1.12 (PB0)
PD4: D11.2 (A), U1.2 (PD4)
RST: C3.2, C12.1, J1.5 (~RST), R1.1, SW1.2, U1.29 (~RESET/PC6)
RXD: U1.30 (PD0), U3.6 (TXD)
SCK: J1.3 (SCK), U1.17 (PB5), U12.14 (SCK), U13.14 (SCK), U14.14 (SCK)
SCL: J4.3, U1.28 (PC5)
SDA: J4.2, U1.27 (PC4)
TXD: R51.1, U1.31 (PD1)
VehicleStatus: R32.2, R47.1, U1.11 (PD7)
VehicleStatus OUT: D14.2 (A), J3.3, Q12.5 (D), Q12.6 (D), Q12.7 (D), Q12.8 (D), R52.2
XTAL1: C10.2, R5.2, U1.7 (XTAL1/PB6), Y1.2
XTAL2: C11.2, R5.1, U1.8 (XTAL2/PB7), Y1.1

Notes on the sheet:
RST
CONNECTORS
OPAMP ADC INPUT
RTD BUZZER
ISP
Debug led
2576&1117
VCU STATUS
LIGHT MOSFET
CAN MODULE
USB
BRAKE
328
